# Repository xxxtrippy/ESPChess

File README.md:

<div align="center">

<br/>

**A hand-built 9×9 electronic chessboard** — 81 mechanical key switches, one
addressable RGB LED per square, and an ESP32-S3 running a full chess engine with
variants, clocks, selectable-strength AI and a championship ladder.

<br/>

<sub>Translucent keycaps lit by the piece-colour code · black case · USB-C port</sub>

</div>

---

## Highlights

- ♟️ **Full chess engine** — legal move generation verified by **perft** (startpos
  depth 5 = 4,865,609 nodes; kiwipete depth 4 = 4,085,603). Castling, en passant,
  promotion, check / checkmate / stalemate, 50-move & insufficient-material draws.
- 🎮 **8 game types × 3 opponent modes = 24 configurations.**
- 🤖 **10 AI strength levels** (depth + blunder profiles) with a **championship
  ladder** — win advances, draw rematches, loss restarts at level 1.
- 🌈 **81 addressable RGB LEDs** — per-piece colours, active/waiting brightness,
  move highlights, check indicator, and an evaluation / clock bar on the edge
  segments.
- 🧪 **Portable, test-first core** — the chess/game logic has **zero Arduino
  dependencies** and is validated by a **71-assertion host test suite** before it
  ever touches hardware.
- 🔧 **Open hardware** — KiCad PCBs, 3D-printable plates, and hand-wiring diagrams
  all included.

## Game modes

| Game type | Rules | Clock |
|---|---|---|
| Standard | standard chess | untimed |
| Rapid | standard chess | 15 \| 10 |
| Blitz | standard chess | 5 \| 0 |
| Bullet | standard chess | 1 \| 0 |
| Puzzle | random legal position | untimed |
| Fog of War | enemy piece identities hidden | untimed |
| Horde | 36-pawn horde vs full army | untimed |
| King of the Hill | reach a centre square to win | untimed |

Each is playable as **2 Players**, **Vs AI** (level 1–10), or **Championship**.

## Repository layout

```
espchess/
├── firmware/            PlatformIO project (ESP32-S3, Arduino framework)
│   ├── include/ src/    portable game core + ESP32 HAL glue
│   └── test/            71-assert host suite, perft, play-through demo
├── hardware/
│   ├── pcb/             KiCad: plate board + control board, renders, BOM
│   ├── enclosure/       3D-printable top + bottom plates (STL + generator)
│   └── wiring/          hand-wiring diagrams (matrix + LED chain)
└── docs/                logo + design notes
```

## Hardware

Built on a **KP Republic 9×9 (182×182 mm) switch-tester plate**. Two routes are
provided: a **custom PCB** (plate board + small control board) or **hand-wiring**
the matrix and LED chain directly.

<div align="center">

</div>

**Per square:** 1× MX switch, 1× 1N4148 matrix diode, 1× 5 mm WS2811 addressable
RGB LED — **all through-hole, hand-solderable** (no SMD). The 81 LEDs are chained
in a serpentine order that matches the firmware's `ledIndex()`.

<table>
<tr>
<td align="center"><br/><sub>LED serpentine daisy-chain</sub></td>
<td align="center"><br/><sub>9×9 switch + diode matrix</sub></td>
</tr>
</table>

- **PCB** — [`hardware/pcb/`](hardware/pcb) · open the KiCad projects; see the
  [PCB README](hardware/pcb/README.md) for the matrix map, ribbon pinout and BOM.
- **Enclosure** — [`hardware/enclosure/`](hardware/enclosure) · a two-part printed
  case: switches snap into `top_plate.stl`, the PCB solders to them, and the unit
  screws into `base_enclosure.stl` (one-piece floor + walls + corner posts with M3
  heat-set inserts and a **12 mm battery bay** under the PCB).

> ⚠️ **Verify before building:** the GPIO map in
> [`firmware/include/config.h`](firmware/include/config.h) and the addressable-LED
> pinout are **provisional** — confirm both against your exact board and LEDs.
> Power the LEDs from an external 5 V supply (up to ~4 A at full white), never the
> ESP32 rail.

## Firmware

### Build & flash

```bash
# device (PlatformIO):
cd firmware
pio run            # compile for ESP32-S3
pio run -t upload  # flash
pio device monitor # 115200 baud
```

### Run the test suite on your PC (no hardware)

```bash
cd firmware
./run_host_tests.sh
```

```
71 unit/integration tests PASS   (0 fail)  — incl. all 24 game configs
20/20 perft positions PASS
```

### Playing

Tap your piece, then its destination (legal targets glow green), and press **your
clock** to commit the move. **M** resets the game. Mode selection is on the serial
console today (`g` game · `o` opponent · `l` level · `c` colour · `n` start) — an
on-board menu on the edge-segment LEDs is the next UI step.

## How it's verified

The engine is proven by **perft** — exhaustively counting the legal-move tree from
known positions and matching published node counts to the last node. On top of
that, the suite drives the real game controller through full games (scripted
checkmates, AI self-play to completion in every mode) and checks the clocks,
variants, LED mapping and championship ladder. See
[`firmware/test/`](firmware/test) and the captured
[test output](firmware/test/HOST_TEST_OUTPUT.txt) /
[play-through log](firmware/test/DEMO_PLAYTHROUGH.txt).

## Roadmap

- [ ] On-board menu (game type / level on the E1–E7 · S1–S7 segment LEDs)
- [ ] Under-promotion select (currently auto-queens)
- [ ] Puzzle-solving scoring semantics
- [ ] Hardware bring-up: confirm pinout, LED pinout, power, flash & play

## License

MIT — see [LICENSE](LICENSE).

<div align="center"><sub>Built for the love of over-engineering a chessboard. ♚</sub></div>

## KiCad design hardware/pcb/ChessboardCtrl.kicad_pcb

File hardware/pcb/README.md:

# 9×9 Chessboard PCB — KP Republic 182×182 mm plate

Two‑board KiCad 8 design, all **through‑hole** (hand‑solderable, no SMD):

1. **PLATE board** `ChessboardPCB` — 182×182 mm, mounts the 81 MX switches of the
   KP Republic 9×9 switch‑tester plate, with one 5 mm addressable RGB LED and one
   1N4148 matrix diode per switch. Connects to the control board by a ribbon (J1).
2. **CONTROL board** `ChessboardCtrl` — 70×55 mm, holds the ESP32 breakout,
   74AHCT125 level shifter, data resistor, bulk cap and 5 V input. Connects to the
   plate board by the matching ribbon (J2).

The switch grid fills the plate (152.4 mm span in 182 mm → ~14.8 mm margins), so
the control electronics live on their own small board instead of being crammed
into the edge.

## Files

- `ChessboardPCB.kicad_pcb` / `.kicad_pro` — plate board (open in KiCad 8).
- `ChessboardCtrl.kicad_pcb` / `.kicad_pro` — control board.
- `plate_render.png`, `ctrl_render.png` — top‑view renders.
- `matrix_map.csv` — per switch: physical row/col, ROW/COL net, LED chain index,
  chess square (A1–H8) or control role (M, E1–E7, S1–S7, clocks).
- `BOM.csv` — parts for both boards.

**State:** both boards are fully **placed and netlisted** (full ratsnest in
KiCad). **Tracks are not routed yet** — see “Finish the boards”. Footprints are
custom and embedded (library names `Chessboard:*` / `Ctrl:*`), so the projects
open with no external libraries; verify the custom ones before a full build.

## Board orientation (matches the firmware handoff — authoritative)

White at the bottom, Black at the top, never rotated.

- Physical `row 0` = **top** (Black). `row 8` = **bottom** (White).
- `(0,0)` = **M**. `(0,8)` = **BLACK CLK**. `(8,0)` = **WHITE CLK**.
- `(0,1..7)` = E1–E7. `(1..7,0)` = S1–S7.
- Chess squares `(1..8,1..8)`: `A1 = (8,1)` bottom‑left, `H8 = (1,8)` top‑right.
- `SW{n}` and `D{n}` are numbered `row*9 + col + 1`.

Plate centred on the board: 19.05 mm pitch, M3 holes in the corners.

## Matrix wiring (plate board)

9 rows × 9 cols, one 1N4148 per key:

```
COL(c) ── switch ── SWD_r_c ── 1N4148(anode→cathode) ── ROW(r)
```

Diode pad 1 is the banded (cathode) end → `ROW(r)`. **Diode direction and
which lines you drive vs. read must match your `config.h` scan code** (the
handoff flags this). Keep the pin map configurable, not hard‑coded.

## LED chain (plate board)

81 × 5 mm addressable LEDs (WS2811 driver inside, WS2812‑compatible). They are
daisy‑chained in the exact serpentine your firmware already uses, so
`ledIndex()` is guaranteed correct by the layout:

```cpp
uint16_t ledIndex(uint8_t row, uint8_t col) {
    if ((row & 1) == 0) return row * 9 + col;   // even rows L→R
    return row * 9 + (8 - col);                 // odd rows R→L
}
```

`LED1` (index 0) is at `(0,0)`; the data signal snakes row by row to index 80.
Data arrives from the control board as `DATA_LED` (already level‑shifted and
through the series resistor).

## The ribbon between the boards (J1 ⇄ J2, 2×13, identical order)

| Pin | Net | Pin | Net |
|----|-------|----|-------|
| 1  | ROW0  | 14 | COL0 |
| 2  | ROW1  | 15 | COL1 |
| 3  | ROW2  | 16 | COL2 |
| 4  | ROW3  | 17 | COL3 |
| 5  | ROW4  | 18 | COL4 |
| 6  | ROW5  | 19 | COL5 |
| 7  | ROW6  | 20 | COL6 |
| 8  | ROW7  | 21 | COL7 |
| 9  | ROW8  | 22 | COL8 |
| 10 | +5V   | 23 | +5V  |
| 11 | GND   | 24 | GND  |
| 12 | DATA_LED | 25 | +5V |
| 13 | DOUT_END | 26 | GND |

Use a 26‑way IDC ribbon (or pin‑to‑pin). `DOUT_END` is the last LED’s DOUT,
brought back for diagnostics — leave unconnected if unused. Power pins are
trebled (3× +5V, 3× GND) so the ribbon can carry LED current; for full
brightness consider feeding 5 V to the plate directly as well.

## Control board (ChessboardCtrl)

- **J3** — 2×11 ESP32‑S3 breakout. Flylead/dupont to the dev board. Left column:
  ROW0–8, GND, +5V. Right column: COL0–8, MCU_DATA, GND. Wire to whatever GPIOs
  you set in `config.h`; the handoff’s provisional pins (rows 1–10, cols 11–21,
  data 47) are **unverified** — confirm against your module’s strapping/boot pins.
- **U1** 74AHCT125 (DIP‑14) — shifts the ESP32 3.3 V data to 5 V. Buffer 1 used:
  1OE→GND (enabled), 1A←MCU_DATA, 1Y→DATA_SHIFTED; unused buffers disabled.
- **R1** 470 Ω — series on the data line (DATA_SHIFTED → DATA_LED).
- **C1** 1000 µF — bulk cap across 5 V / GND.
- **J4** — 5 V input (from your external supply).
- **J2** — ribbon to the plate (pinout above).

## Power (read before building)

- 81 LEDs at full white draw **~50 mA each ≈ 4 A @ 5 V worst case.** **Do not
  power the LEDs from the ESP32 3.3 V rail or USB alone.**
- Feed regulated **5 V** into **J4** on the control board; share a **common
  ground** with the ESP32.
- Cap brightness/current in firmware so you never actually reach 4 A. For full
  brightness, also inject 5 V/GND straight onto the plate’s +5V/GND, don’t rely
  on the ribbon alone.
- When routing, give +5V/GND wide tracks or copper pours.

## Finish the boards in KiCad (routing)

1. Open each `.kicad_pro` in **KiCad 8** → PCB editor. Everything is placed; the
   white ratsnest shows all connections.
2. Plate board — fastest clean matrix route: **ROWs** horizontal on **B.Cu**,
   **COLs** vertical on **F.Cu** (they cross only on opposite layers); add **GND
   and +5V copper pours** on both layers; route the short LED `CHAIN*` data hops
   last. Or export **Specctra DSN** and autoroute with Freerouting.
3. Control board — a handful of parts, route by hand in minutes.
4. Run **DRC** (clearance 0.2 mm / track 0.3 mm) on both, fix, then Gerbers.

## Verify before building (custom footprints)

1. **Addressable LED pinout — most important.** Footprint pads, left→right, are
   **`+5V, DIN, GND, DOUT`** (pin‑1 `+5V` marked on silk). Vendor pinouts differ —
   check your LED’s datasheet and swap pad/net assignment if needed. The 4 leads
   form to a 2.54 mm inline pitch for hand‑soldering.
2. **MX switch** — standard Cherry pin positions, 4 mm centre hole, two 1.75 mm
   leg holes; plate‑mount (3‑pin) and 5‑pin PCB‑mount both drop in. Fit‑test one
   against your plate first.
3. **1N4148** — DO‑35, 7.62 mm pitch; band (cathode) = pad 1 = ROW side.
4. Build and test **one full cell + a 3‑LED chain** before populating all 81.

## Enclosure — 3D-printed sandwich (top plate · PCB · bottom plate)

`top_plate.stl`, `bottom_plate.stl` (previews: `plates_top_view.png`,
`sandwich_section.png`). Both are 182×182 mm and share the PCB's 4 corner M3
holes.

Stack, top to bottom:

```
TOP PLATE (3mm, 81 MX cutouts)
   └─ 3.5mm gap  ← set by the SWITCH itself (corner legs are printed spacers)
PCB (1.6mm)
   └─ 6mm M3 standoff ×4  ← clears bottom-side pins / solder / LED legs
BOTTOM PLATE (3mm, flat)
```

**Key constraint — the top gap is not free.** An MX switch fixes the
plate‑to‑PCB distance at ~3.4–3.5 mm, so you **cannot** put a tall motherboard
standoff between the top plate and the PCB — the pins wouldn't reach. The top
plate therefore has four **3.5 mm corner legs** printed on its underside that
rest on the PCB and keep the plate parallel; the switches carry the rest. The
**M3 standoffs go between the PCB and the bottom plate**, where the height is
free (6 mm clears the trimmed pins and solder).

Top-plate switch holes are **stepped**: a 1.5 mm latch web (14 mm opening) on
top so the MX clips actually snap in, opening to 15.6 mm relief below so the
clips can spring. Print the top plate **web-side up** (holes get a 0.8 mm
down-facing ledge that bridges fine, no supports).

Fasteners per corner:
- **M3×12** from the top: through top plate + corner leg + PCB, into the
  standoff's top thread.
- **M3×6** from the bottom: through the bottom plate into the standoff's bottom
  thread.
- 4× **M3 6 mm female-female** standoffs.

Print notes: PETG or PLA, ~0.2 mm layers, 3+ walls. Check one switch fits a test
cutout before printing the whole plate — tune `MX_CUT` (14.0) and the 3.5 mm leg
height in `scripts/gen_plates.py` to your switches/printer, then re-run. The
bottom plate has a 24×10 mm cable slot centered on one edge for the ESP32 lead.

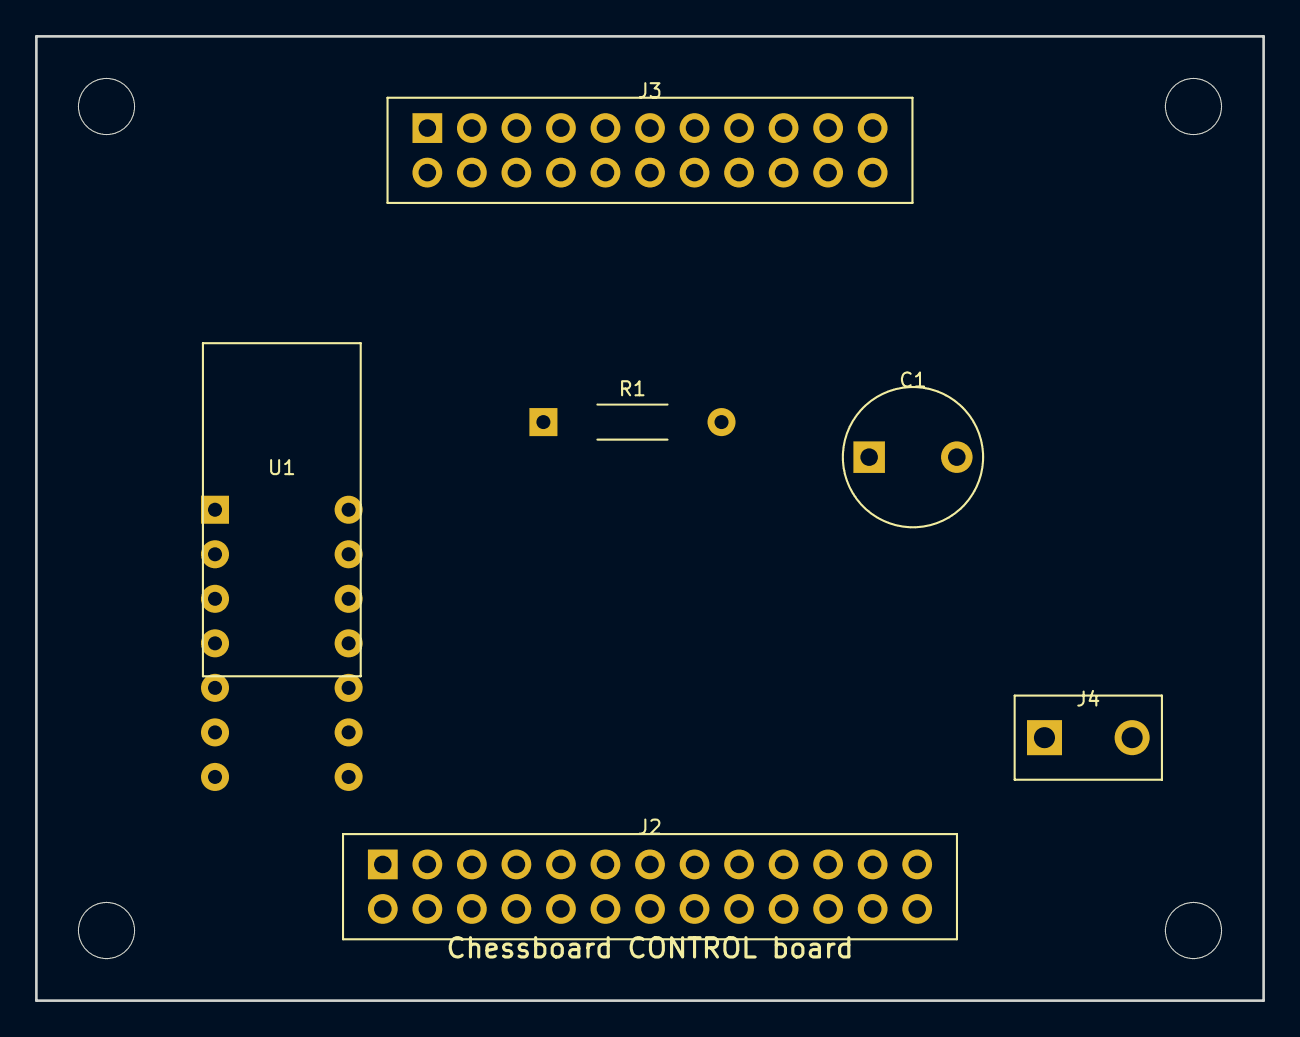
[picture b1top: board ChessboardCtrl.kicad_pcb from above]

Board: 2 copper layers, 70.0 x 55.0 mm, 6 parts (0 on the bottom side), 23 nets, no tracks yet.

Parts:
C1: 1000uF 16V; CP_Radial_1000uF
J2: TO_PLATE; Interconnect_2x13
J3: ESP32_IO; ESP32_Breakout_2x11
J4: 5V IN; PWR_5V_IN
R1: 470R; R_AXIAL
U1: 74AHCT125; DIP14_74AHCT125

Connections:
+5V: C1.1, J2.10, J2.23, J2.25, J3.11, J4.1, U1.4, U1.10, U1.13, U1.14
COL0: J2.14, J3.12
COL1: J2.15, J3.13
COL2: J2.16, J3.14
COL3: J2.17, J3.15
COL4: J2.18, J3.16
COL5: J2.19, J3.17
COL6: J2.20, J3.18
COL7: J2.21, J3.19
COL8: J2.22, J3.20
DATA_LED: J2.12, R1.2
DATA_SHIFTED: R1.1, U1.3
GND: C1.2, J2.11, J2.24, J2.26, J3.10, J3.22, J4.2, U1.1, U1.5, U1.7, U1.9, U1.12
MCU_DATA: J3.21, U1.2
ROW0: J2.1, J3.1
ROW1: J2.2, J3.2
ROW2: J2.3, J3.3
ROW3: J2.4, J3.4
ROW4: J2.5, J3.5
ROW5: J2.6, J3.6
ROW6: J2.7, J3.7
ROW7: J2.8, J3.8
ROW8: J2.9, J3.9

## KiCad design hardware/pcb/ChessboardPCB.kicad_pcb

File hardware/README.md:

# ESPChess — Hardware

Everything to build the board, two ways: a **custom PCB** or **hand-wiring**.

## Contents

| Folder | What |
|---|---|
| [`pcb/`](pcb) | KiCad 8 projects — the **plate board** (`ChessboardPCB`, 182×182 mm, all 81 switches + LEDs + diodes) and the **control board** (`ChessboardCtrl`, ESP32 breakout + level shifter + power). Renders, BOM and matrix map included. See [pcb/README.md](pcb/README.md). |
| [`enclosure/`](enclosure) | 3D-printable two-part case — `top_plate.stl` (flat switch plate the switches snap into) and `base_enclosure.stl` (one-piece floor + walls + corner posts with a 12 mm battery bay). `gen_case.py` regenerates them. |
| [`wiring/`](wiring) | Hand-wiring diagrams for the 9×9 matrix and the serpentine LED chain. |

## The enclosure

The switches snap into the **top plate**; the **PCB is soldered to the switch
pins**, making plate + switches + PCB one rigid unit. That unit drops into the
**base** and is held by 4× M3 screws through the plate corners (and the PCB) into
**heat-set brass inserts** in the base's corner posts.

```
TOP PLATE (4 mm, 81 stepped MX cutouts, counterbored screw holes) — snap-in switches
   └─ 3.5 mm switch gap   (printed corner legs set it)
PCB (soldered to switches)
   └─ 12 mm battery bay    (open floor between the corner posts)
BASE (one piece: 3 mm floor + 5 mm walls + 4 corner posts w/ M3 inserts)
```

Outer footprint 193 × 193 mm, assembled height ≈ 24 mm. A **Ø12 mm port**,
centred side-to-side and top-to-bottom on one wall, opens into the battery bay
(USB / power / switch).

<table>
<tr>
<td align="center"><br/><sub>Base</sub></td>
<td align="center"><br/><sub>Top plate</sub></td>
</tr>
<tr>
<td align="center"><br/><sub>Assembled</sub></td>
<td align="center"><br/><sub>Exploded</sub></td>
</tr>
</table>

**Hardware:** 4× M3 heat-set inserts (≈4.0 mm pilot), 4× M3×14–16 socket-head
screws. Print the top plate **web-side up** (the switch cutouts' 0.8 mm ledge
bridges without supports); print the base floor-down.

## Per-square parts (×81)

| Part | Value | Note |
|---|---|---|
| Switch | Cherry MX (or clone) | plate/PCB mount |
| Diode | 1N4148 (DO-35) | matrix anti-ghosting |
| LED | 5 mm WS2811 addressable RGB | through-hole; **verify 4-pin order** |

Plus one 470 Ω data resistor, a 74AHCT125 level shifter, a 1000 µF bulk cap, and
an external **5 V supply** (size for ~4 A at full white). Full BOM in
[`pcb/BOM.csv`](pcb/BOM.csv).

> ⚠️ The GPIO map and LED pinout are **provisional** — confirm against your exact
> board before committing solder.

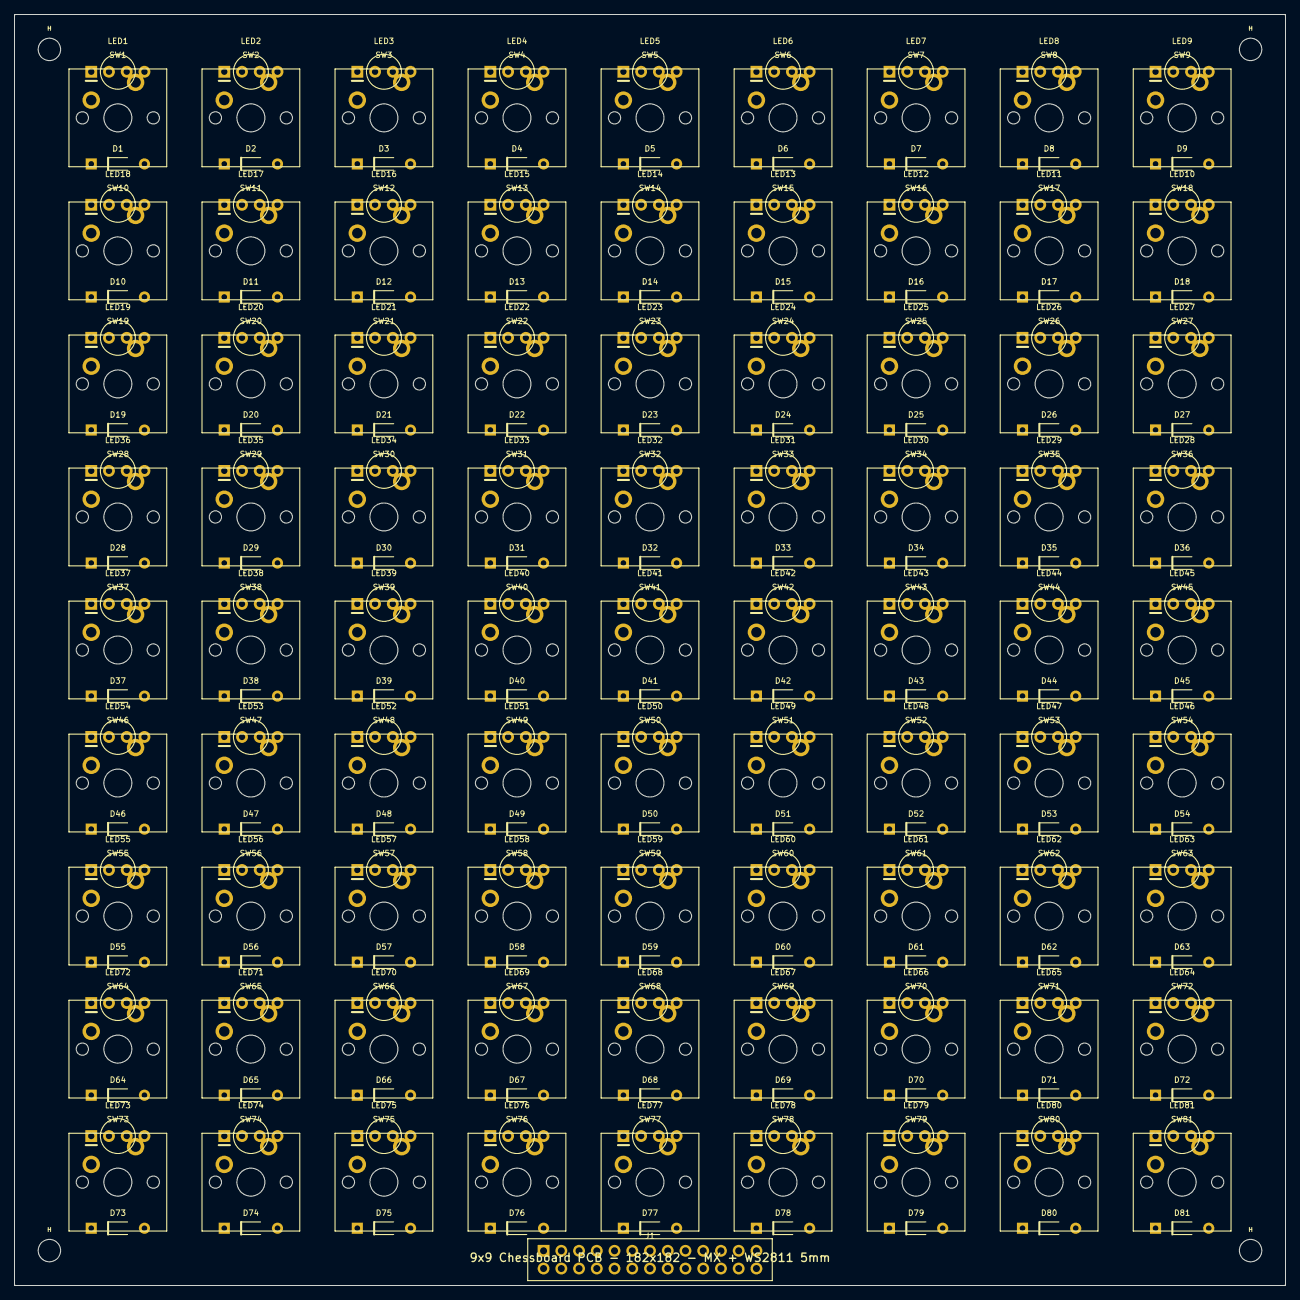
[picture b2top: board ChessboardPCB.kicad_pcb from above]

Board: 2 copper layers, 182.0 x 182.0 mm, 248 parts (0 on the bottom side), 183 nets, no tracks yet.

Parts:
D1, D2, D3, D4, D5, D6, D7, D8, D9, D10, D11, D12, D13, D14, D15, D16, D17, D18, D19, D20, D21, D22, D23, D24, D25, D26, D27, D28, D29, D30, D31, D32, D33, D34, D35, D36, D37, D38, D39, D40, D41, D42, D43, D44, D45, D46, D47, D48, D49, D50, D51, D52, D53, D54, D55, D56, D57, D58, D59, D60, D61, D62, D63, D64, D65, D66, D67, D68, D69, D70, D71, D72, D73, D74, D75, D76, D77, D78, D79, D80, D81: 1N4148; D_1N4148_DO35
H: M3; MountingHole_3mm
H#2, H#3, H#4: M3; MountingHole_3mm
J1: TO_CTRL_BD; Interconnect_2x13
LED1: WS2811_i0; LED_RGB_5mm_WS2811
LED2: WS2811_i1; LED_RGB_5mm_WS2811
LED3: WS2811_i2; LED_RGB_5mm_WS2811
LED4: WS2811_i3; LED_RGB_5mm_WS2811
LED5: WS2811_i4; LED_RGB_5mm_WS2811
LED6: WS2811_i5; LED_RGB_5mm_WS2811
LED7: WS2811_i6; LED_RGB_5mm_WS2811
LED8: WS2811_i7; LED_RGB_5mm_WS2811
LED9: WS2811_i8; LED_RGB_5mm_WS2811
LED10: WS2811_i9; LED_RGB_5mm_WS2811
LED11: WS2811_i10; LED_RGB_5mm_WS2811
LED12: WS2811_i11; LED_RGB_5mm_WS2811
LED13: WS2811_i12; LED_RGB_5mm_WS2811
LED14: WS2811_i13; LED_RGB_5mm_WS2811
LED15: WS2811_i14; LED_RGB_5mm_WS2811
LED16: WS2811_i15; LED_RGB_5mm_WS2811
LED17: WS2811_i16; LED_RGB_5mm_WS2811
LED18: WS2811_i17; LED_RGB_5mm_WS2811
LED19: WS2811_i18; LED_RGB_5mm_WS2811
LED20: WS2811_i19; LED_RGB_5mm_WS2811
LED21: WS2811_i20; LED_RGB_5mm_WS2811
LED22: WS2811_i21; LED_RGB_5mm_WS2811
LED23: WS2811_i22; LED_RGB_5mm_WS2811
LED24: WS2811_i23; LED_RGB_5mm_WS2811
LED25: WS2811_i24; LED_RGB_5mm_WS2811
LED26: WS2811_i25; LED_RGB_5mm_WS2811
LED27: WS2811_i26; LED_RGB_5mm_WS2811
LED28: WS2811_i27; LED_RGB_5mm_WS2811
LED29: WS2811_i28; LED_RGB_5mm_WS2811
LED30: WS2811_i29; LED_RGB_5mm_WS2811
LED31: WS2811_i30; LED_RGB_5mm_WS2811
LED32: WS2811_i31; LED_RGB_5mm_WS2811
LED33: WS2811_i32; LED_RGB_5mm_WS2811
LED34: WS2811_i33; LED_RGB_5mm_WS2811
LED35: WS2811_i34; LED_RGB_5mm_WS2811
LED36: WS2811_i35; LED_RGB_5mm_WS2811
LED37: WS2811_i36; LED_RGB_5mm_WS2811
LED38: WS2811_i37; LED_RGB_5mm_WS2811
LED39: WS2811_i38; LED_RGB_5mm_WS2811
LED40: WS2811_i39; LED_RGB_5mm_WS2811
LED41: WS2811_i40; LED_RGB_5mm_WS2811
LED42: WS2811_i41; LED_RGB_5mm_WS2811
LED43: WS2811_i42; LED_RGB_5mm_WS2811
LED44: WS2811_i43; LED_RGB_5mm_WS2811
LED45: WS2811_i44; LED_RGB_5mm_WS2811
LED46: WS2811_i45; LED_RGB_5mm_WS2811
LED47: WS2811_i46; LED_RGB_5mm_WS2811
LED48: WS2811_i47; LED_RGB_5mm_WS2811
LED49: WS2811_i48; LED_RGB_5mm_WS2811
LED50: WS2811_i49; LED_RGB_5mm_WS2811
LED51: WS2811_i50; LED_RGB_5mm_WS2811
LED52: WS2811_i51; LED_RGB_5mm_WS2811
LED53: WS2811_i52; LED_RGB_5mm_WS2811
LED54: WS2811_i53; LED_RGB_5mm_WS2811
LED55: WS2811_i54; LED_RGB_5mm_WS2811
LED56: WS2811_i55; LED_RGB_5mm_WS2811
LED57: WS2811_i56; LED_RGB_5mm_WS2811
LED58: WS2811_i57; LED_RGB_5mm_WS2811
LED59: WS2811_i58; LED_RGB_5mm_WS2811
LED60: WS2811_i59; LED_RGB_5mm_WS2811
LED61: WS2811_i60; LED_RGB_5mm_WS2811
LED62: WS2811_i61; LED_RGB_5mm_WS2811
LED63: WS2811_i62; LED_RGB_5mm_WS2811
LED64: WS2811_i63; LED_RGB_5mm_WS2811
LED65: WS2811_i64; LED_RGB_5mm_WS2811
LED66: WS2811_i65; LED_RGB_5mm_WS2811
LED67: WS2811_i66; LED_RGB_5mm_WS2811
LED68: WS2811_i67; LED_RGB_5mm_WS2811
LED69: WS2811_i68; LED_RGB_5mm_WS2811
LED70: WS2811_i69; LED_RGB_5mm_WS2811
LED71: WS2811_i70; LED_RGB_5mm_WS2811
LED72: WS2811_i71; LED_RGB_5mm_WS2811
LED73: WS2811_i72; LED_RGB_5mm_WS2811
LED74: WS2811_i73; LED_RGB_5mm_WS2811
LED75: WS2811_i74; LED_RGB_5mm_WS2811
LED76: WS2811_i75; LED_RGB_5mm_WS2811
LED77: WS2811_i76; LED_RGB_5mm_WS2811
LED78: WS2811_i77; LED_RGB_5mm_WS2811
LED79: WS2811_i78; LED_RGB_5mm_WS2811
LED80: WS2811_i79; LED_RGB_5mm_WS2811
LED81: WS2811_i80; LED_RGB_5mm_WS2811
SW1: MX_0_0; SW_MX
SW2: MX_0_1; SW_MX
SW3: MX_0_2; SW_MX
SW4: MX_0_3; SW_MX
SW5: MX_0_4; SW_MX
SW6: MX_0_5; SW_MX
SW7: MX_0_6; SW_MX
SW8: MX_0_7; SW_MX
SW9: MX_0_8; SW_MX
SW10: MX_1_0; SW_MX
SW11: MX_1_1; SW_MX
SW12: MX_1_2; SW_MX
SW13: MX_1_3; SW_MX
SW14: MX_1_4; SW_MX
SW15: MX_1_5; SW_MX
SW16: MX_1_6; SW_MX
SW17: MX_1_7; SW_MX
SW18: MX_1_8; SW_MX
SW19: MX_2_0; SW_MX
SW20: MX_2_1; SW_MX
SW21: MX_2_2; SW_MX
SW22: MX_2_3; SW_MX
SW23: MX_2_4; SW_MX
SW24: MX_2_5; SW_MX
SW25: MX_2_6; SW_MX
SW26: MX_2_7; SW_MX
SW27: MX_2_8; SW_MX
SW28: MX_3_0; SW_MX
SW29: MX_3_1; SW_MX
SW30: MX_3_2; SW_MX
SW31: MX_3_3; SW_MX
SW32: MX_3_4; SW_MX
SW33: MX_3_5; SW_MX
SW34: MX_3_6; SW_MX
SW35: MX_3_7; SW_MX
SW36: MX_3_8; SW_MX
SW37: MX_4_0; SW_MX
SW38: MX_4_1; SW_MX
SW39: MX_4_2; SW_MX
SW40: MX_4_3; SW_MX
SW41: MX_4_4; SW_MX
SW42: MX_4_5; SW_MX
SW43: MX_4_6; SW_MX
SW44: MX_4_7; SW_MX
SW45: MX_4_8; SW_MX
SW46: MX_5_0; SW_MX
SW47: MX_5_1; SW_MX
SW48: MX_5_2; SW_MX
SW49: MX_5_3; SW_MX
SW50: MX_5_4; SW_MX
SW51: MX_5_5; SW_MX
SW52: MX_5_6; SW_MX
SW53: MX_5_7; SW_MX
SW54: MX_5_8; SW_MX
SW55: MX_6_0; SW_MX
SW56: MX_6_1; SW_MX
SW57: MX_6_2; SW_MX
SW58: MX_6_3; SW_MX
SW59: MX_6_4; SW_MX
SW60: MX_6_5; SW_MX
SW61: MX_6_6; SW_MX
SW62: MX_6_7; SW_MX
SW63: MX_6_8; SW_MX
SW64: MX_7_0; SW_MX
SW65: MX_7_1; SW_MX
SW66: MX_7_2; SW_MX
SW67: MX_7_3; SW_MX
SW68: MX_7_4; SW_MX
SW69: MX_7_5; SW_MX
SW70: MX_7_6; SW_MX
SW71: MX_7_7; SW_MX
SW72: MX_7_8; SW_MX
SW73: MX_8_0; SW_MX
SW74: MX_8_1; SW_MX
SW75: MX_8_2; SW_MX
SW76: MX_8_3; SW_MX
SW77: MX_8_4; SW_MX
SW78: MX_8_5; SW_MX
SW79: MX_8_6; SW_MX
SW80: MX_8_7; SW_MX
SW81: MX_8_8; SW_MX

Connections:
+5V: J1.10, J1.23, J1.25, LED1.1, LED2.1, LED3.1, LED4.1, LED5.1, LED6.1, LED7.1, LED8.1, LED9.1, LED10.1, LED11.1, LED12.1, LED13.1, LED14.1, LED15.1, LED16.1, LED17.1, LED18.1, LED19.1, LED20.1, LED21.1, LED22.1, LED23.1, LED24.1, LED25.1, LED26.1, LED27.1, LED28.1, LED29.1, LED30.1, LED31.1, LED32.1, LED33.1, LED34.1, LED35.1, LED36.1, LED37.1, LED38.1, LED39.1, LED40.1, LED41.1, LED42.1, LED43.1, LED44.1, LED45.1, LED46.1, LED47.1, LED48.1, LED49.1, LED50.1, LED51.1, LED52.1, LED53.1, LED54.1, LED55.1, LED56.1, LED57.1, LED58.1, LED59.1, LED60.1, LED61.1, LED62.1, LED63.1, LED64.1, LED65.1, LED66.1, LED67.1, LED68.1, LED69.1, LED70.1, LED71.1, LED72.1, LED73.1, LED74.1, LED75.1, LED76.1, LED77.1, LED78.1, LED79.1, LED80.1, LED81.1
CHAIN0: LED1.4, LED2.2
CHAIN1: LED2.4, LED3.2
CHAIN2: LED3.4, LED4.2
CHAIN3: LED4.4, LED5.2
CHAIN4: LED5.4, LED6.2
CHAIN5: LED6.4, LED7.2
CHAIN6: LED7.4, LED8.2
CHAIN7: LED8.4, LED9.2
CHAIN8: LED9.4, LED10.2
CHAIN9: LED10.4, LED11.2
CHAIN10: LED11.4, LED12.2
CHAIN11: LED12.4, LED13.2
CHAIN12: LED13.4, LED14.2
CHAIN13: LED14.4, LED15.2
CHAIN14: LED15.4, LED16.2
CHAIN15: LED16.4, LED17.2
CHAIN16: LED17.4, LED18.2
CHAIN17: LED18.4, LED19.2
CHAIN18: LED19.4, LED20.2
CHAIN19: LED20.4, LED21.2
CHAIN20: LED21.4, LED22.2
CHAIN21: LED22.4, LED23.2
CHAIN22: LED23.4, LED24.2
CHAIN23: LED24.4, LED25.2
CHAIN24: LED25.4, LED26.2
CHAIN25: LED26.4, LED27.2
CHAIN26: LED27.4, LED28.2
CHAIN27: LED28.4, LED29.2
CHAIN28: LED29.4, LED30.2
CHAIN29: LED30.4, LED31.2
CHAIN30: LED31.4, LED32.2
CHAIN31: LED32.4, LED33.2
CHAIN32: LED33.4, LED34.2
CHAIN33: LED34.4, LED35.2
CHAIN34: LED35.4, LED36.2
CHAIN35: LED36.4, LED37.2
CHAIN36: LED37.4, LED38.2
CHAIN37: LED38.4, LED39.2
CHAIN38: LED39.4, LED40.2
CHAIN39: LED40.4, LED41.2
CHAIN40: LED41.4, LED42.2
CHAIN41: LED42.4, LED43.2
CHAIN42: LED43.4, LED44.2
CHAIN43: LED44.4, LED45.2
CHAIN44: LED45.4, LED46.2
CHAIN45: LED46.4, LED47.2
CHAIN46: LED47.4, LED48.2
CHAIN47: LED48.4, LED49.2
CHAIN48: LED49.4, LED50.2
CHAIN49: LED50.4, LED51.2
CHAIN50: LED51.4, LED52.2
CHAIN51: LED52.4, LED53.2
CHAIN52: LED53.4, LED54.2
CHAIN53: LED54.4, LED55.2
CHAIN54: LED55.4, LED56.2
CHAIN55: LED56.4, LED57.2
CHAIN56: LED57.4, LED58.2
CHAIN57: LED58.4, LED59.2
CHAIN58: LED59.4, LED60.2
CHAIN59: LED60.4, LED61.2
CHAIN60: LED61.4, LED62.2
CHAIN61: LED62.4, LED63.2
CHAIN62: LED63.4, LED64.2
CHAIN63: LED64.4, LED65.2
CHAIN64: LED65.4, LED66.2
CHAIN65: LED66.4, LED67.2
CHAIN66: LED67.4, LED68.2
CHAIN67: LED68.4, LED69.2
CHAIN68: LED69.4, LED70.2
CHAIN69: LED70.4, LED71.2
CHAIN70: LED71.4, LED72.2
CHAIN71: LED72.4, LED73.2
CHAIN72: LED73.4, LED74.2
CHAIN73: LED74.4, LED75.2
CHAIN74: LED75.4, LED76.2
CHAIN75: LED76.4, LED77.2
CHAIN76: LED77.4, LED78.2
CHAIN77: LED78.4, LED79.2
CHAIN78: LED79.4, LED80.2
CHAIN79: LED80.4, LED81.2
COL0: J1.14, SW1.1, SW10.1, SW19.1, SW28.1, SW37.1, SW46.1, SW55.1, SW64.1, SW73.1
COL1: J1.15, SW2.1, SW11.1, SW20.1, SW29.1, SW38.1, SW47.1, SW56.1, SW65.1, SW74.1
COL2: J1.16, SW3.1, SW12.1, SW21.1, SW30.1, SW39.1, SW48.1, SW57.1, SW66.1, SW75.1
COL3: J1.17, SW4.1, SW13.1, SW22.1, SW31.1, SW40.1, SW49.1, SW58.1, SW67.1, SW76.1
COL4: J1.18, SW5.1, SW14.1, SW23.1, SW32.1, SW41.1, SW50.1, SW59.1, SW68.1, SW77.1
COL5: J1.19, SW6.1, SW15.1, SW24.1, SW33.1, SW42.1, SW51.1, SW60.1, SW69.1, SW78.1
COL6: J1.20, SW7.1, SW16.1, SW25.1, SW34.1, SW43.1, SW52.1, SW61.1, SW70.1, SW79.1
COL7: J1.21, SW8.1, SW17.1, SW26.1, SW35.1, SW44.1, SW53.1, SW62.1, SW71.1, SW80.1
COL8: J1.22, SW9.1, SW18.1, SW27.1, SW36.1, SW45.1, SW54.1, SW63.1, SW72.1, SW81.1
DATA_LED: J1.12, LED1.2
DOUT_END: J1.13, LED81.4
GND: J1.11, J1.24, J1.26, LED1.3, LED2.3, LED3.3, LED4.3, LED5.3, LED6.3, LED7.3, LED8.3, LED9.3, LED10.3, LED11.3, LED12.3, LED13.3, LED14.3, LED15.3, LED16.3, LED17.3, LED18.3, LED19.3, LED20.3, LED21.3, LED22.3, LED23.3, LED24.3, LED25.3, LED26.3, LED27.3, LED28.3, LED29.3, LED30.3, LED31.3, LED32.3, LED33.3, LED34.3, LED35.3, LED36.3, LED37.3, LED38.3, LED39.3, LED40.3, LED41.3, LED42.3, LED43.3, LED44.3, LED45.3, LED46.3, LED47.3, LED48.3, LED49.3, LED50.3, LED51.3, LED52.3, LED53.3, LED54.3, LED55.3, LED56.3, LED57.3, LED58.3, LED59.3, LED60.3, LED61.3, LED62.3, LED63.3, LED64.3, LED65.3, LED66.3, LED67.3, LED68.3, LED69.3, LED70.3, LED71.3, LED72.3, LED73.3, LED74.3, LED75.3, LED76.3, LED77.3, LED78.3, LED79.3, LED80.3, LED81.3
ROW0: D1.1, D2.1, D3.1, D4.1, D5.1, D6.1, D7.1, D8.1, D9.1, J1.1
ROW1: D10.1, D11.1, D12.1, D13.1, D14.1, D15.1, D16.1, D17.1, D18.1, J1.2
ROW2: D19.1, D20.1, D21.1, D22.1, D23.1, D24.1, D25.1, D26.1, D27.1, J1.3
ROW3: D28.1, D29.1, D30.1, D31.1, D32.1, D33.1, D34.1, D35.1, D36.1, J1.4
ROW4: D37.1, D38.1, D39.1, D40.1, D41.1, D42.1, D43.1, D44.1, D45.1, J1.5
ROW5: D46.1, D47.1, D48.1, D49.1, D50.1, D51.1, D52.1, D53.1, D54.1, J1.6
ROW6: D55.1, D56.1, D57.1, D58.1, D59.1, D60.1, D61.1, D62.1, D63.1, J1.7
ROW7: D64.1, D65.1, D66.1, D67.1, D68.1, D69.1, D70.1, D71.1, D72.1, J1.8
ROW8: D73.1, D74.1, D75.1, D76.1, D77.1, D78.1, D79.1, D80.1, D81.1, J1.9
SWD_0_0: D1.2, SW1.2
SWD_0_1: D2.2, SW2.2
SWD_0_2: D3.2, SW3.2
SWD_0_3: D4.2, SW4.2
SWD_0_4: D5.2, SW5.2
SWD_0_5: D6.2, SW6.2
SWD_0_6: D7.2, SW7.2
SWD_0_7: D8.2, SW8.2
SWD_0_8: D9.2, SW9.2
SWD_1_0: D10.2, SW10.2
SWD_1_1: D11.2, SW11.2
SWD_1_2: D12.2, SW12.2
SWD_1_3: D13.2, SW13.2
SWD_1_4: D14.2, SW14.2
SWD_1_5: D15.2, SW15.2
SWD_1_6: D16.2, SW16.2
SWD_1_7: D17.2, SW17.2
SWD_1_8: D18.2, SW18.2
SWD_2_0: D19.2, SW19.2
SWD_2_1: D20.2, SW20.2
SWD_2_2: D21.2, SW21.2
SWD_2_3: D22.2, SW22.2
SWD_2_4: D23.2, SW23.2
SWD_2_5: D24.2, SW24.2
SWD_2_6: D25.2, SW25.2
SWD_2_7: D26.2, SW26.2
SWD_2_8: D27.2, SW27.2
SWD_3_0: D28.2, SW28.2
SWD_3_1: D29.2, SW29.2
SWD_3_2: D30.2, SW30.2
SWD_3_3: D31.2, SW31.2
SWD_3_4: D32.2, SW32.2
SWD_3_5: D33.2, SW33.2
SWD_3_6: D34.2, SW34.2
SWD_3_7: D35.2, SW35.2
SWD_3_8: D36.2, SW36.2
SWD_4_0: D37.2, SW37.2
SWD_4_1: D38.2, SW38.2
SWD_4_2: D39.2, SW39.2
SWD_4_3: D40.2, SW40.2
SWD_4_4: D41.2, SW41.2
SWD_4_5: D42.2, SW42.2
SWD_4_6: D43.2, SW43.2
SWD_4_7: D44.2, SW44.2
SWD_4_8: D45.2, SW45.2
SWD_5_0: D46.2, SW46.2
SWD_5_1: D47.2, SW47.2
SWD_5_2: D48.2, SW48.2
SWD_5_3: D49.2, SW49.2
SWD_5_4: D50.2, SW50.2
SWD_5_5: D51.2, SW51.2
SWD_5_6: D52.2, SW52.2
SWD_5_7: D53.2, SW53.2
SWD_5_8: D54.2, SW54.2
SWD_6_0: D55.2, SW55.2
SWD_6_1: D56.2, SW56.2
SWD_6_2: D57.2, SW57.2
SWD_6_3: D58.2, SW58.2
SWD_6_4: D59.2, SW59.2
SWD_6_5: D60.2, SW60.2
SWD_6_6: D61.2, SW61.2
SWD_6_7: D62.2, SW62.2
SWD_6_8: D63.2, SW63.2
SWD_7_0: D64.2, SW64.2
SWD_7_1: D65.2, SW65.2
SWD_7_2: D66.2, SW66.2
SWD_7_3: D67.2, SW67.2
SWD_7_4: D68.2, SW68.2
SWD_7_5: D69.2, SW69.2
SWD_7_6: D70.2, SW70.2
SWD_7_7: D71.2, SW71.2
SWD_7_8: D72.2, SW72.2
SWD_8_0: D73.2, SW73.2
SWD_8_1: D74.2, SW74.2
SWD_8_2: D75.2, SW75.2
SWD_8_3: D76.2, SW76.2
SWD_8_4: D77.2, SW77.2
SWD_8_5: D78.2, SW78.2
SWD_8_6: D79.2, SW79.2
SWD_8_7: D80.2, SW80.2
SWD_8_8: D81.2, SW81.2
